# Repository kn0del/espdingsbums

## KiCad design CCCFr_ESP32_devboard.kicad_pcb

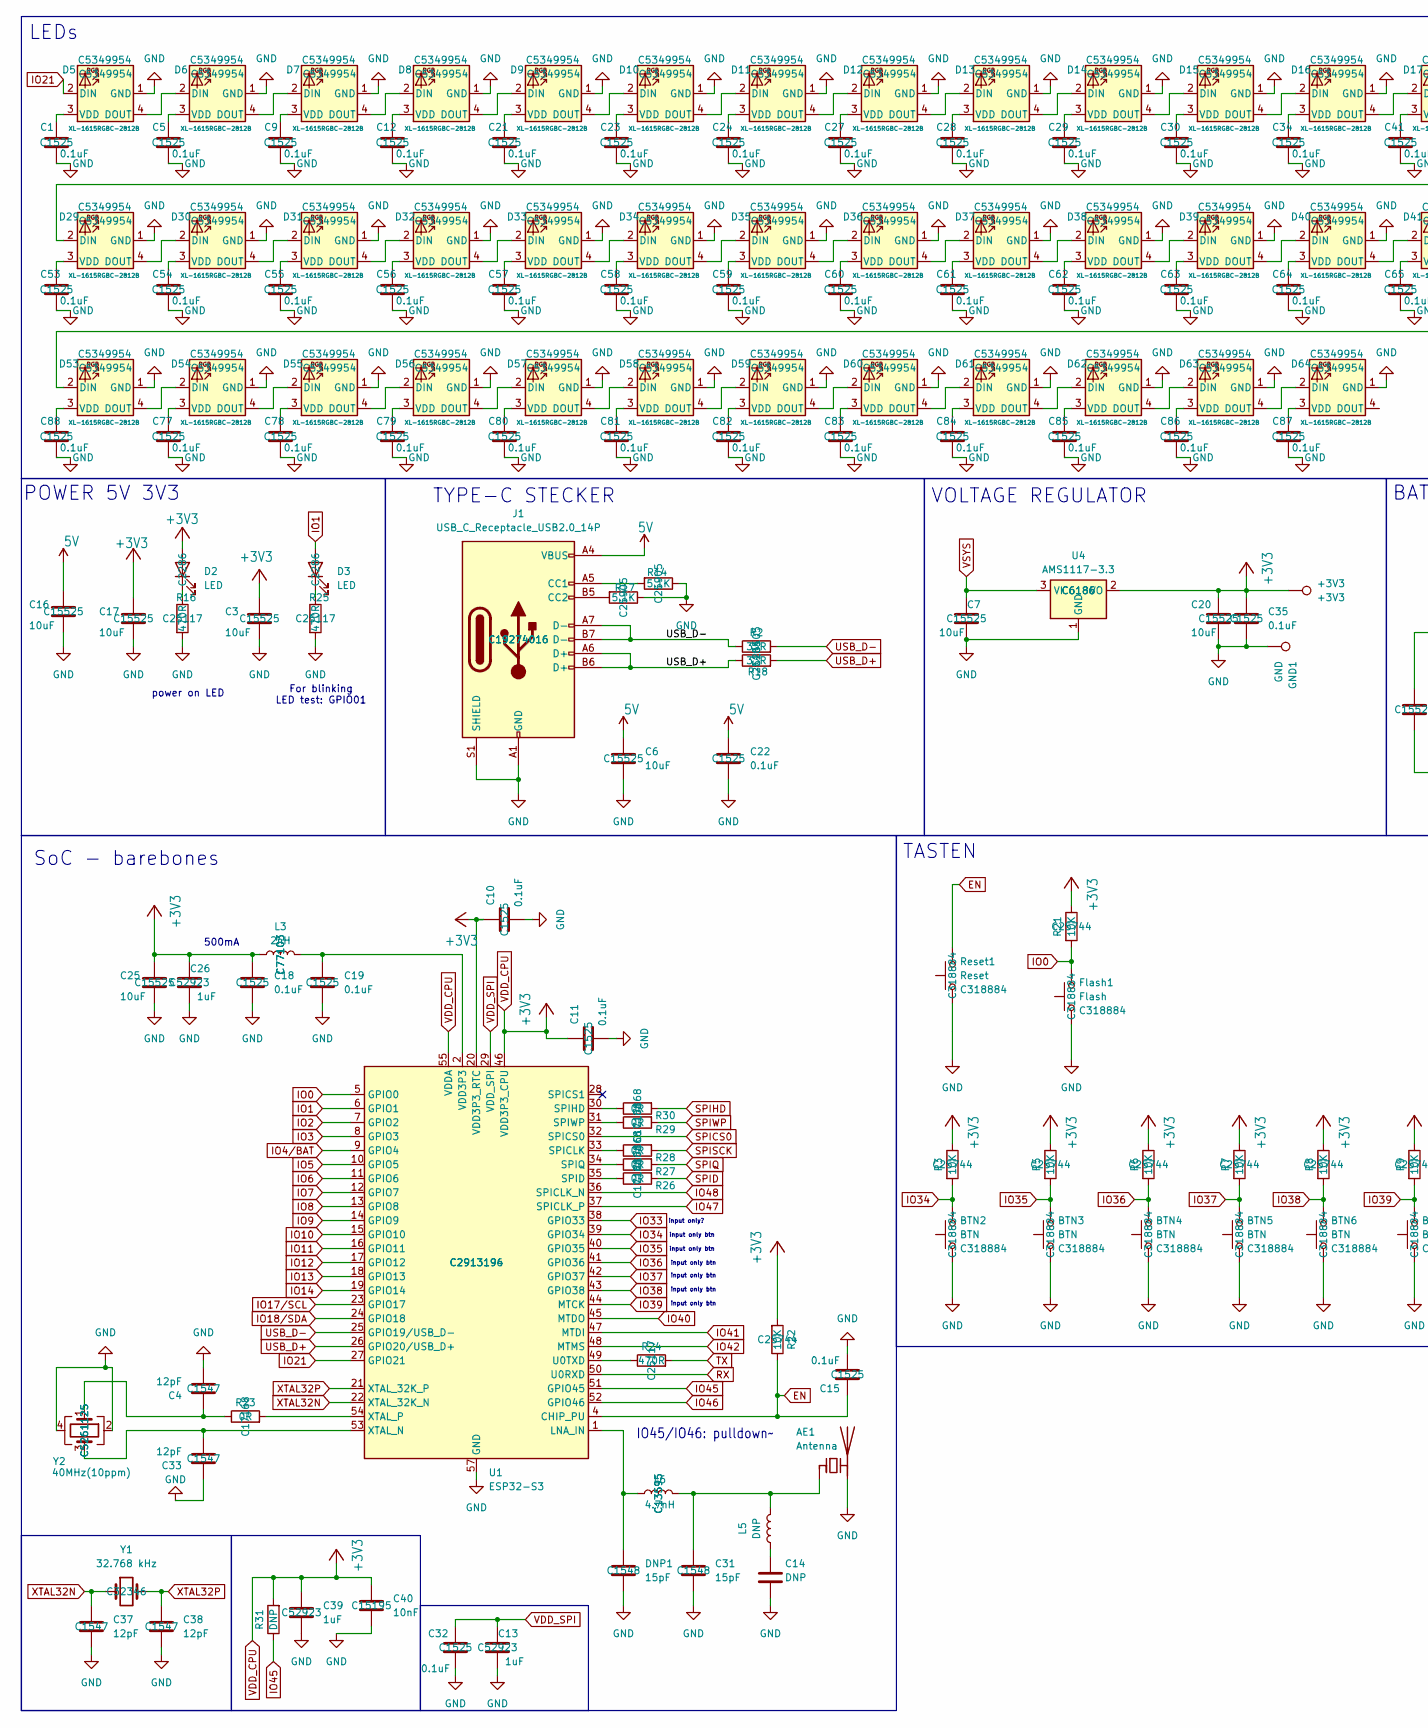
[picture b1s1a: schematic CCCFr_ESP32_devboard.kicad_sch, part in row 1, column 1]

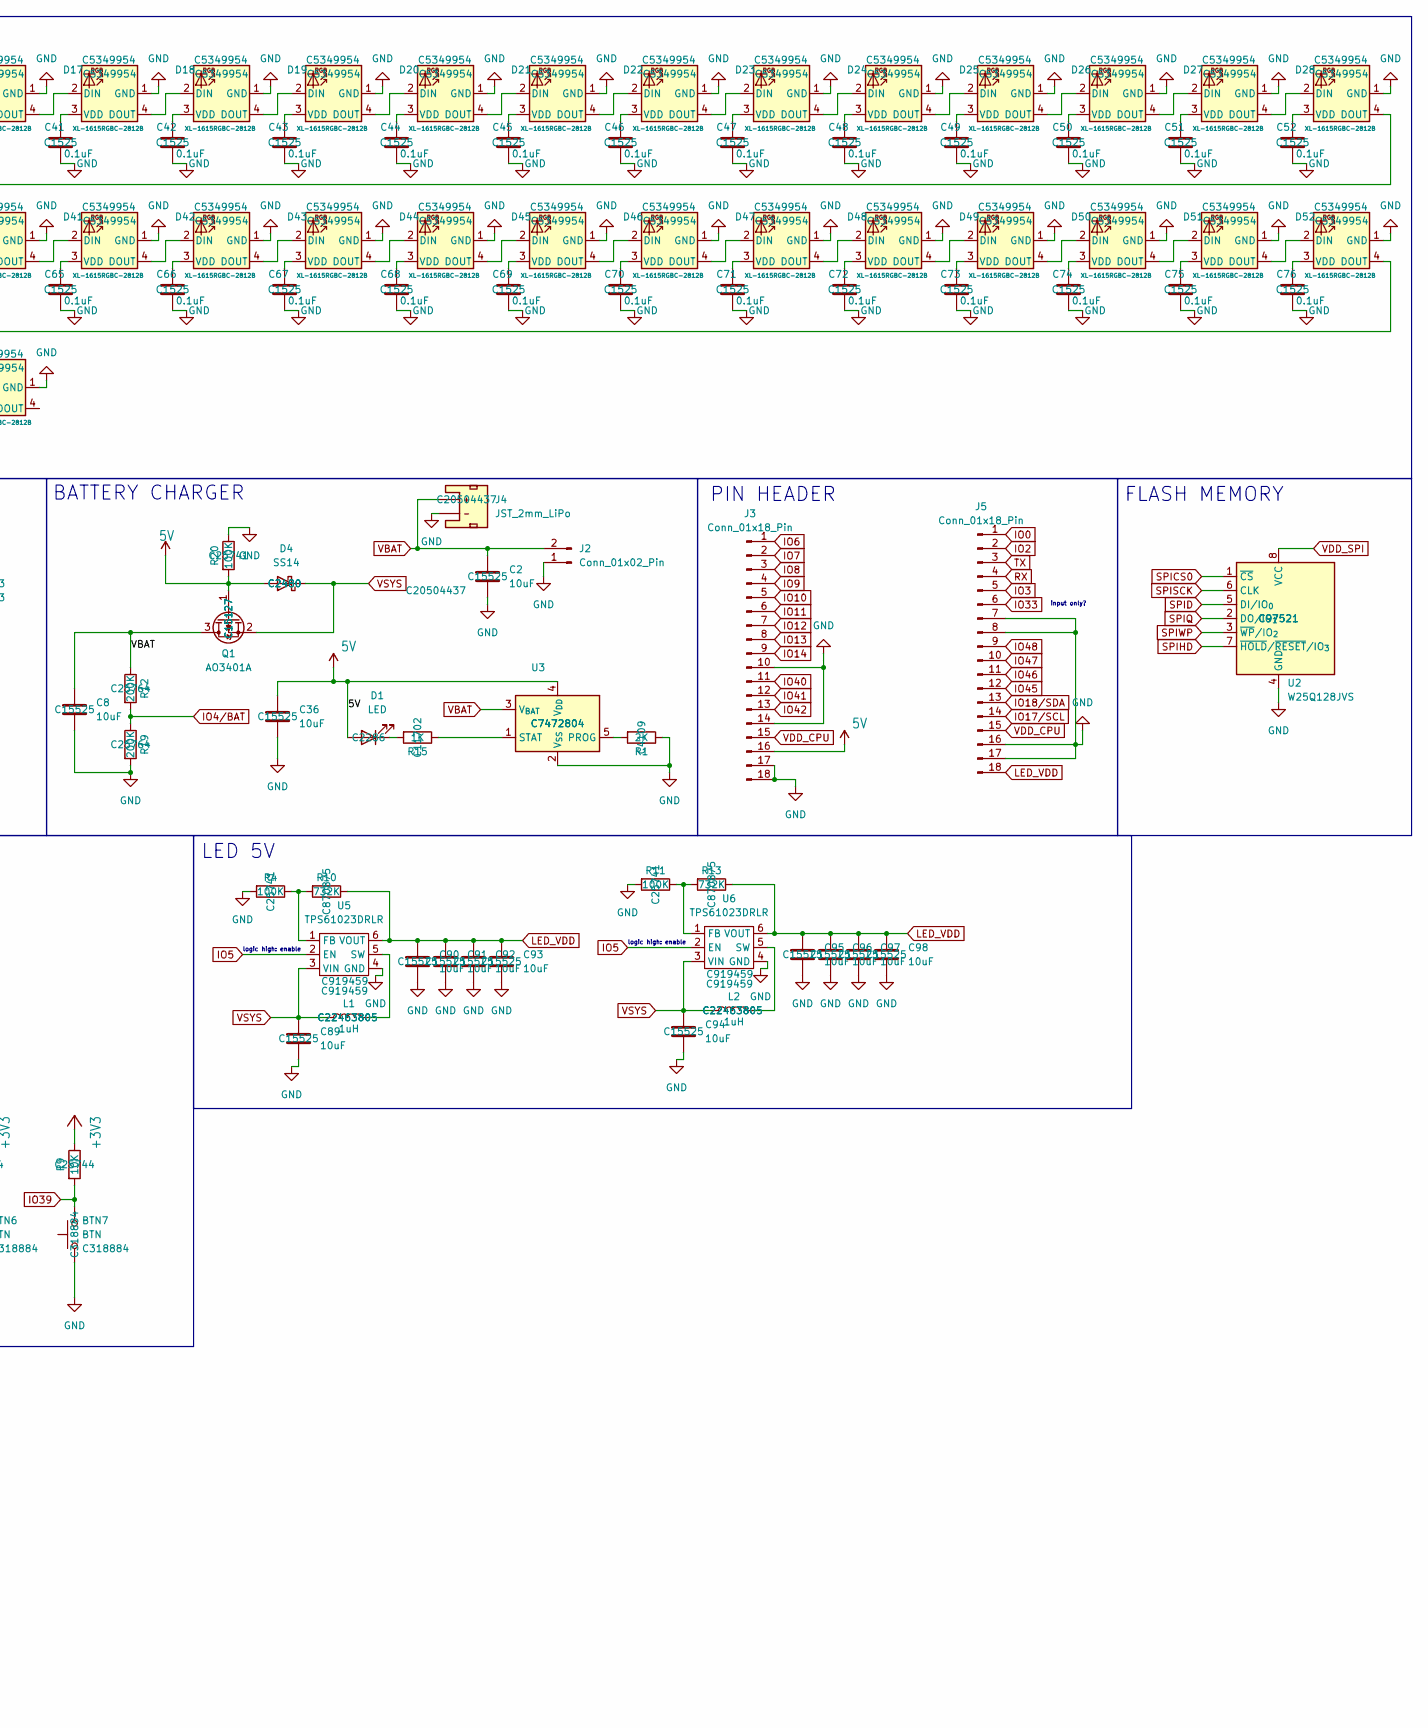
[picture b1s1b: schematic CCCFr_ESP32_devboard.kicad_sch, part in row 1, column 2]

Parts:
+3V3: +3V3; TestPoint_Pad_D1.0mm
AE1: Antenna; Texas_SWRA117D_2.4GHz_Left
BTN2, BTN3, BTN4, BTN5, BTN6, BTN7: BTN; SW_Push_1P1T_XKB_TS-1187A; MNF PART NUMBER C318884; LCSC C318884
C1, C5, C9, C10, C11, C12, C15, C18, C19, C21, C22, C23, C24, C27, C28, C29, C30, C32, C34, C35, C41, C42, C43, C44, C45, C46, C47, C48, C49, C50, C51, C52, C53, C54, C55, C56, C57, C58, C59, C60, C61, C62, C63, C64, C65, C66, C67, C68, C69, C70, C71, C72, C73, C74, C75, C76, C77, C78, C79, C80, C81, C82, C83, C84, C85, C86, C87, C88: 0.1uF; C_0402_1005Metric; MNF PART NUMBER C1525; LCSC C1525
C2, C3, C6, C7, C8, C16, C17, C20, C25, C36, C89, C90, C91, C92, C93, C94, C95, C96, C97, C98: 10uF; C_0402_1005Metric; MNF PART NUMBER C15525; LCSC C15525
C4, C33, C37, C38: 12pF; C_0402_1005Metric; MNF PART NUMBER C1547; LCSC C1547
C13, C26, C39: 1uF; C_0402_1005Metric; MNF PART NUMBER C52923; LCSC C52923
C14: DNP; C_0402_1005Metric
C31: 15pF; C_0402_1005Metric; MNF PART NUMBER C1548; LCSC C1548
C40: 10nF; C_0402_1005Metric; MNF PART NUMBER C15195; LCSC C15195
D1, D2, D3: LED; LED_0603_1608Metric; MNF PART NUMBER C2286; LCSC C2286
D4: SS14; D_SMA; MNF PART NUMBER C2480; LCSC C2480
D5, D6, D7, D8, D9, D10, D11, D12, D13, D14, D15, D16, D17, D18, D19, D20, D21, D22, D23, D24, D25, D26, D27, D28, D29, D30, D31, D32, D33, D34, D35, D36, D37, D38, D39, D40, D41, D42, D43, D44, D45, D46, D47, D48, D49, D50, D51, D52, D53, D54, D55, D56, D57, D58, D59, D60, D61, D62, D63, D64: XL-1615RGBC-2812B; MNF PART NUMBER C5349954; LCSC C5349954
DNP1: 15pF; C_0402_1005Metric; MNF PART NUMBER C1548; LCSC C1548
Flash1: Flash; SW_Push_1P1T_XKB_TS-1187A; MNF PART NUMBER C318884; LCSC C318884
GND1: GND; TestPoint_Pad_D1.0mm
J1: USB_C_Receptacle_USB2.0_14P; USB_C_Receptacle_HCTL_HC-TYPE-C-16P-01A; MNF PART NUMBER C19274016; LCSC C19274016
J2: Conn_01x02_Pin; PinSocket_1x02_P2.54mm_Vertical
J3, J5: Conn_01x18_Pin; PinHeader_1x18_P2.54mm_Vertical
J4: JST_2mm_LiPo; JST_PH_B2B-PH-K_1x02_P2.00mm_Vertical; MNF PART NUMBER C20504437; LCSC C20504437
L1, L2: 1uH; L_TechFuse_SL0420; MNF PART NUMBER C22463805; LCSC C22463805
L3: 2nH; L_0402_1005Metric; MNF PART NUMBER C77103; LCSC C77103
L5: DNP; L_0402_1005Metric
L6: 4.7nH; L_0402_1005Metric; MNF PART NUMBER C13595; LCSC C13595
Q1: AO3401A; SOT-23; MNF PART NUMBER C15127; LCSC C15127
R1: 2K; R_0402_1005Metric; MNF PART NUMBER C4109; LCSC C4109
R2, R18: 33R; R_0402_1005Metric; MNF PART NUMBER C25105; LCSC C25105
R3, R5, R6, R7, R8, R9, R21, R22: 10K; R_0402_1005Metric; MNF PART NUMBER C25744; LCSC C25744
R4, R11, R20: 100K; R_0402_1005Metric; MNF PART NUMBER C25741; LCSC C25741
R10, R13: 732K; R_1206_3216Metric; MNF PART NUMBER C870875; LCSC C870875
R12, R19: 200K; R_0402_1005Metric; MNF PART NUMBER C25764; LCSC C25764
R14, R17: 5.1K; R_0402_1005Metric; MNF PART NUMBER C25905; LCSC C25905
R15: 1K; R_0402_1005Metric; MNF PART NUMBER C11702; LCSC C11702
R16, R24, R25: 470R; R_0402_1005Metric; MNF PART NUMBER C25117; LCSC C25117
R23, R26, R27, R28, R29, R30: 0R; R_0402_1005Metric; MNF PART NUMBER C17168; LCSC C17168
R31: DNP; R_0402_1005Metric
Reset1: Reset; SW_Push_1P1T_XKB_TS-1187A; MNF PART NUMBER C318884; LCSC C318884
U1: ESP32-S3; QFN-56-1EP_7x7mm_P0.4mm_EP4x4mm; MNF PART NUMBER C2913196; LCSC C2913194
U2: W25Q128JVS; SOIC-8_5.3x5.3mm_P1.27mm; MNF PART NUMBER C97521; LCSC C97521
U3: MCP73831-2-OT; SOT-23-5; MNF PART NUMBER C7472804; LCSC C7472804
U4: AMS1117-3.3; SOT-223-3_TabPin2; MNF PART NUMBER C6186; LCSC C6186
U5, U6: TPS61023DRLR; SOT-563; MNF PART NUMBER C919459; LCSC C919459
Y1: 32.768 kHz; Crystal_SMD_3215-2Pin_3.2x1.5mm; MNF PART NUMBER C32346; LCSC C32346
Y2: 40MHz(10ppm); Crystal_SMD_2520-4Pin_2.5x2.0mm; MNF PART NUMBER C5261125; LCSC C5261125

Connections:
5V: C6.1, C16.1, C22.1, C36.1, D1.2 (A), D4.2 (A), J1.A4 (VBUS), J1.A9 (VBUS), J1.B4 (VBUS), J1.B9 (VBUS), J3.16, Q1.1 (G), R20.2, U3.4 (V_{DD})
EN: C15.1, R22.1, Reset1.2, U1.4 (CHIP_PU)
GND: AE1.2 (PCB_Trace), BTN2.1, BTN3.1, BTN4.1, BTN5.1, BTN6.1, BTN7.1, C1.2, C2.2, C3.2, C4.2, C5.2, C6.2, C7.2, C8.2, C9.2, C10.2, C11.2, C12.2, C13.2, C14.2, C15.2, C16.2, C17.2, C18.2, C19.2, C20.2, C21.2, C22.2, C23.2, C24.2, C25.2, C26.2, C27.2, C28.2, C29.2, C30.2, C31.2, C32.2, C33.1, C34.2, C35.2, C36.2, C37.2, C38.2, C39.2, C40.2, C41.2, C42.2, C43.2, C44.2, C45.2, C46.2, C47.2, C48.2, C49.2, C50.2, C51.2, C52.2, C53.2, C54.2, C55.2, C56.2, C57.2, C58.2, C59.2, C60.2, C61.2, C62.2, C63.2, C64.2, C65.2, C66.2, C67.2, C68.2, C69.2, C70.2, C71.2, C72.2, C73.2, C74.2, C75.2, C76.2, C77.2, C78.2, C79.2, C80.2, C81.2, C82.2, C83.2, C84.2, C85.2, C86.2, C87.2, C88.2, C89.2, C90.2, C91.2, C92.2, C93.2, C94.2, C95.2, C96.2, C97.2, C98.2, D5.1 (GND), D6.1 (GND), D7.1 (GND), D8.1 (GND), D9.1 (GND), D10.1 (GND), D11.1 (GND), D12.1 (GND), D13.1 (GND), D14.1 (GND), D15.1 (GND), D16.1 (GND), D17.1 (GND), D18.1 (GND), D19.1 (GND), D20.1 (GND), D21.1 (GND), D22.1 (GND), D23.1 (GND), D24.1 (GND), D25.1 (GND), D26.1 (GND), D27.1 (GND), D28.1 (GND), D29.1 (GND), D30.1 (GND), D31.1 (GND), D32.1 (GND), D33.1 (GND), D34.1 (GND), D35.1 (GND), D36.1 (GND), D37.1 (GND), D38.1 (GND), D39.1 (GND), D40.1 (GND), D41.1 (GND), D42.1 (GND), D43.1 (GND), D44.1 (GND), D45.1 (GND), D46.1 (GND), D47.1 (GND), D48.1 (GND), D49.1 (GND), D50.1 (GND), D51.1 (GND), D52.1 (GND), D53.1 (GND), D54.1 (GND), D55.1 (GND), D56.1 (GND), D57.1 (GND), D58.1 (GND), D59.1 (GND), D60.1 (GND), D61.1 (GND), D62.1 (GND), D63.1 (GND), D64.1 (GND), DNP1.2, Flash1.1, GND1.1, J1.A1 (GND), J1.A12 (GND), J1.B1 (GND), J1.B12 (GND), J1.S1 (SHIELD), J2.1, J3.10, J3.14, J3.17, J3.18, J4.1 (-), J5.7, J5.8, J5.16, J5.17, R1.1, R4.2, R11.2, R14.1, R16.2, R17.1, R19.2, R20.1, R25.2, Reset1.1, U1.57 (GND), U2.4 (GND), U3.2 (V_{SS}), U4.1 (GND), U5.4 (GND), U6.4 (GND), Y2.2, Y2.4
IO0: Flash1.2, J5.1, R21.2, U1.5 (GPIO0)
IO1: D3.2 (A), U1.6 (GPIO1)
IO2: J5.2, U1.7 (GPIO2)
IO3: J5.5, U1.8 (GPIO3)
IO4/BAT: R12.2, R19.1, U1.9 (GPIO4)
IO5: U1.10 (GPIO5), U5.2 (EN), U6.2 (EN)
IO6: J3.1, U1.11 (GPIO6)
IO7: J3.2, U1.12 (GPIO7)
IO8: J3.3, U1.13 (GPIO8)
IO9: J3.4, U1.14 (GPIO9)
IO10: J3.5, U1.15 (GPIO10)
IO11: J3.6, U1.16 (GPIO11)
IO12: J3.7, U1.17 (GPIO12)
IO13: J3.8, U1.18 (GPIO13)
IO14: J3.9, U1.19 (GPIO14)
IO17/SCL: J5.14, U1.23 (GPIO17)
IO18/SDA: J5.13, U1.24 (GPIO18)
IO21: D5.2 (DIN), U1.27 (GPIO21)
IO33: J5.6, U1.38 (GPIO33)
IO34: BTN2.2, R3.2, U1.39 (GPIO34)
IO35: BTN3.2, R5.2, U1.40 (GPIO35)
IO36: BTN4.2, R6.2, U1.41 (GPIO36)
IO37: BTN5.2, R7.2, U1.42 (GPIO37)
IO38: BTN6.2, R8.2, U1.43 (GPIO38)
IO39: BTN7.2, R9.2, U1.44 (MTCK)
IO40: J3.11, U1.45 (MTDO)
IO41: J3.12, U1.47 (MTDI)
IO42: J3.13, U1.48 (MTMS)
IO45: J5.12, R31.1, U1.51 (GPIO45)
IO46: J5.11, U1.52 (GPIO46)
IO47: J5.10, U1.37 (SPICLK_P)
IO48: J5.9, U1.36 (SPICLK_N)
LED_VDD: C90.1, C91.1, C92.1, C93.1, C95.1, C96.1, C97.1, C98.1, J5.18, R10.1, R13.1, U5.6 (VOUT), U6.6 (VOUT)
unnamed: AE1.1 (FEED), C31.1, L5.2, L6.2
unnamed: C4.1, R23.1, Y2.1
unnamed: C14.1, L5.1
unnamed: C19.1, L3.2, U1.2 (VDD3P3), U1.3 (VDD3P3)
unnamed: D1.1 (K), R15.2
unnamed: D2.1 (K), R16.1
unnamed: D3.1 (K), R25.1
unnamed: D5.4 (DOUT), D6.2 (DIN)
unnamed: C1.1, D5.3 (VDD)
unnamed: D6.4 (DOUT), D7.2 (DIN)
unnamed: C5.1, D6.3 (VDD)
unnamed: D7.4 (DOUT), D8.2 (DIN)
unnamed: C9.1, D7.3 (VDD)
unnamed: D8.4 (DOUT), D9.2 (DIN)
unnamed: C12.1, D8.3 (VDD)
unnamed: C21.1, D9.3 (VDD)
unnamed: D9.4 (DOUT), D10.2 (DIN)
unnamed: D10.4 (DOUT), D11.2 (DIN)
unnamed: C23.1, D10.3 (VDD)
unnamed: D11.4 (DOUT), D12.2 (DIN)
unnamed: C24.1, D11.3 (VDD)
unnamed: D12.4 (DOUT), D13.2 (DIN)
unnamed: C27.1, D12.3 (VDD)
unnamed: D13.4 (DOUT), D14.2 (DIN)
unnamed: C28.1, D13.3 (VDD)
unnamed: D14.4 (DOUT), D15.2 (DIN)
unnamed: C29.1, D14.3 (VDD)
unnamed: D15.4 (DOUT), D16.2 (DIN)
unnamed: C30.1, D15.3 (VDD)
unnamed: D16.4 (DOUT), D17.2 (DIN)
unnamed: C34.1, D16.3 (VDD)
unnamed: D17.4 (DOUT), D18.2 (DIN)
unnamed: C41.1, D17.3 (VDD)
unnamed: D18.4 (DOUT), D19.2 (DIN)
unnamed: C42.1, D18.3 (VDD)
unnamed: D19.4 (DOUT), D20.2 (DIN)
unnamed: C43.1, D19.3 (VDD)
unnamed: D20.4 (DOUT), D21.2 (DIN)
unnamed: C44.1, D20.3 (VDD)
unnamed: D21.4 (DOUT), D22.2 (DIN)
unnamed: C45.1, D21.3 (VDD)
unnamed: D22.4 (DOUT), D23.2 (DIN)
unnamed: C46.1, D22.3 (VDD)
unnamed: D23.4 (DOUT), D24.2 (DIN)
unnamed: C47.1, D23.3 (VDD)
unnamed: D24.4 (DOUT), D25.2 (DIN)
unnamed: C48.1, D24.3 (VDD)
unnamed: D25.4 (DOUT), D26.2 (DIN)
unnamed: C49.1, D25.3 (VDD)
unnamed: D26.4 (DOUT), D27.2 (DIN)
unnamed: C50.1, D26.3 (VDD)
unnamed: D27.4 (DOUT), D28.2 (DIN)
unnamed: C51.1, D27.3 (VDD)
unnamed: D28.4 (DOUT), D29.2 (DIN)
unnamed: C52.1, D28.3 (VDD)
unnamed: D29.4 (DOUT), D30.2 (DIN)
unnamed: C53.1, D29.3 (VDD)
unnamed: D30.4 (DOUT), D31.2 (DIN)
unnamed: C54.1, D30.3 (VDD)
unnamed: D31.4 (DOUT), D32.2 (DIN)
unnamed: C55.1, D31.3 (VDD)
unnamed: D32.4 (DOUT), D33.2 (DIN)
unnamed: C56.1, D32.3 (VDD)
unnamed: D33.4 (DOUT), D34.2 (DIN)
unnamed: C57.1, D33.3 (VDD)
unnamed: D34.4 (DOUT), D35.2 (DIN)
unnamed: C58.1, D34.3 (VDD)
unnamed: D35.4 (DOUT), D36.2 (DIN)
unnamed: C59.1, D35.3 (VDD)
unnamed: D36.4 (DOUT), D37.2 (DIN)
unnamed: C60.1, D36.3 (VDD)
unnamed: D37.4 (DOUT), D38.2 (DIN)
unnamed: C61.1, D37.3 (VDD)
unnamed: D38.4 (DOUT), D39.2 (DIN)
unnamed: C62.1, D38.3 (VDD)
unnamed: D39.4 (DOUT), D40.2 (DIN)
unnamed: C63.1, D39.3 (VDD)
unnamed: D40.4 (DOUT), D41.2 (DIN)
unnamed: C64.1, D40.3 (VDD)
unnamed: D41.4 (DOUT), D42.2 (DIN)
unnamed: C65.1, D41.3 (VDD)
unnamed: D42.4 (DOUT), D43.2 (DIN)
unnamed: C66.1, D42.3 (VDD)
unnamed: D43.4 (DOUT), D44.2 (DIN)
unnamed: C67.1, D43.3 (VDD)
unnamed: D44.4 (DOUT), D45.2 (DIN)
unnamed: C68.1, D44.3 (VDD)
unnamed: D45.4 (DOUT), D46.2 (DIN)
unnamed: C69.1, D45.3 (VDD)
unnamed: D46.4 (DOUT), D47.2 (DIN)
unnamed: C70.1, D46.3 (VDD)
unnamed: D47.4 (DOUT), D48.2 (DIN)
unnamed: C71.1, D47.3 (VDD)
unnamed: D48.4 (DOUT), D49.2 (DIN)
unnamed: C72.1, D48.3 (VDD)
unnamed: D49.4 (DOUT), D50.2 (DIN)
unnamed: C73.1, D49.3 (VDD)
unnamed: D50.4 (DOUT), D51.2 (DIN)
unnamed: C74.1, D50.3 (VDD)
unnamed: D51.4 (DOUT), D52.2 (DIN)
unnamed: C75.1, D51.3 (VDD)
unnamed: D52.4 (DOUT), D53.2 (DIN)
unnamed: C76.1, D52.3 (VDD)
unnamed: D53.4 (DOUT), D54.2 (DIN)
unnamed: C88.1, D53.3 (VDD)
unnamed: D54.4 (DOUT), D55.2 (DIN)
unnamed: C77.1, D54.3 (VDD)
unnamed: D55.4 (DOUT), D56.2 (DIN)
unnamed: C78.1, D55.3 (VDD)
unnamed: D56.4 (DOUT), D57.2 (DIN)
unnamed: C79.1, D56.3 (VDD)
unnamed: D57.4 (DOUT), D58.2 (DIN)
unnamed: C80.1, D57.3 (VDD)
unnamed: D58.4 (DOUT), D59.2 (DIN)
unnamed: C81.1, D58.3 (VDD)
unnamed: D59.4 (DOUT), D60.2 (DIN)
unnamed: C82.1, D59.3 (VDD)
unnamed: D60.4 (DOUT), D61.2 (DIN)
unnamed: C83.1, D60.3 (VDD)
unnamed: D61.4 (DOUT), D62.2 (DIN)
unnamed: C84.1, D61.3 (VDD)
unnamed: D62.4 (DOUT), D63.2 (DIN)
unnamed: C85.1, D62.3 (VDD)
unnamed: D63.4 (DOUT), D64.2 (DIN)
unnamed: C86.1, D63.3 (VDD)
unnamed: C87.1, D64.3 (VDD)
unnamed: J1.A5 (CC1), R14.2
unnamed: J1.B5 (CC2), R17.2
unnamed: DNP1.1, L6.1, U1.1 (LNA_IN)
unnamed: R28.1, U1.33 (SPICLK)
unnamed: R26.1, U1.35 (SPID)
unnamed: R30.1, U1.30 (SPIHD)
unnamed: R27.1, U1.34 (SPIQ)
unnamed: R29.1, U1.31 (SPIWP)
unnamed: R24.1, U1.49 (U0TXD)
unnamed: C33.2, U1.53 (XTAL_N), Y2.3
unnamed: R23.2, U1.54 (XTAL_P)
unnamed: R1.2, U3.5 (PROG)
unnamed: R15.1, U3.1 (STAT)
unnamed: R4.1, R10.2, U5.1 (FB)
unnamed: L1.2, U5.5 (SW)
unnamed: R11.1, R13.2, U6.1 (FB)
unnamed: L2.2, U6.5 (SW)
RX: J5.4, U1.50 (U0RXD)
SPICS0: U1.32 (SPICS0), U2.1 (~CS)
SPID: R26.2, U2.5 (DI/IO_{0})
SPIHD: R30.2, U2.7 (~HOLD/~RESET/IO_{3})
SPIQ: R27.2, U2.2 (DO/IO_{1})
SPISCK: R28.2, U2.6 (CLK)
SPIWP: R29.2, U2.3 (~WP/IO_{2})
TX: J5.3, R24.2
USB_D+: J1.A6 (D+), J1.B6 (D+), R18.1, R18.2, U1.26 (GPIO20/USB_D+)
USB_D-: J1.A7 (D-), J1.B7 (D-), R2.1, R2.2, U1.25 (GPIO19/USB_D-)
VBAT: C2.1, C8.1, J2.2, J4.2 (+), Q1.3 (D), R12.1, U3.3 (V_{BAT})
VDD_CPU: +3V3.1, C3.1, C10.1, C11.1, C17.1, C18.1, C20.1, C25.1, C26.1, C35.1, C39.1, C40.1, D2.2 (A), J3.15, J5.15, L3.1, R3.1, R5.1, R6.1, R7.1, R8.1, R9.1, R21.1, R22.2, R31.2, U1.20 (VDD3P3_RTC), U1.46 (VDD3P3_CPU), U1.55 (VDDA), U1.56 (VDDA), U4.2 (VO)
VDD_SPI: C13.1, C32.1, U1.29 (VDD_SPI), U2.8 (VCC)
VSYS: C7.1, C89.1, C94.1, D4.1 (K), L1.1, L2.1, Q1.2 (S), U4.3 (VI), U5.3 (VIN), U6.3 (VIN)
XTAL32N: C37.1, U1.22 (XTAL_32K_N), Y1.1
XTAL32P: C38.1, U1.21 (XTAL_32K_P), Y1.2

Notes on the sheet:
BATTERY CHARGER
VOLTAGE REGULATOR
input only btn
power on LED
500mA
LEDs
SoC - barebones
PIN HEADER
FLASH MEMORY
logic high: enable
input only?
LED 5V
TASTEN
For blinking LED test: GPIO01
POWER 5V 3V3
IO45/IO46: pulldown~~{}
TYPE-C STECKER

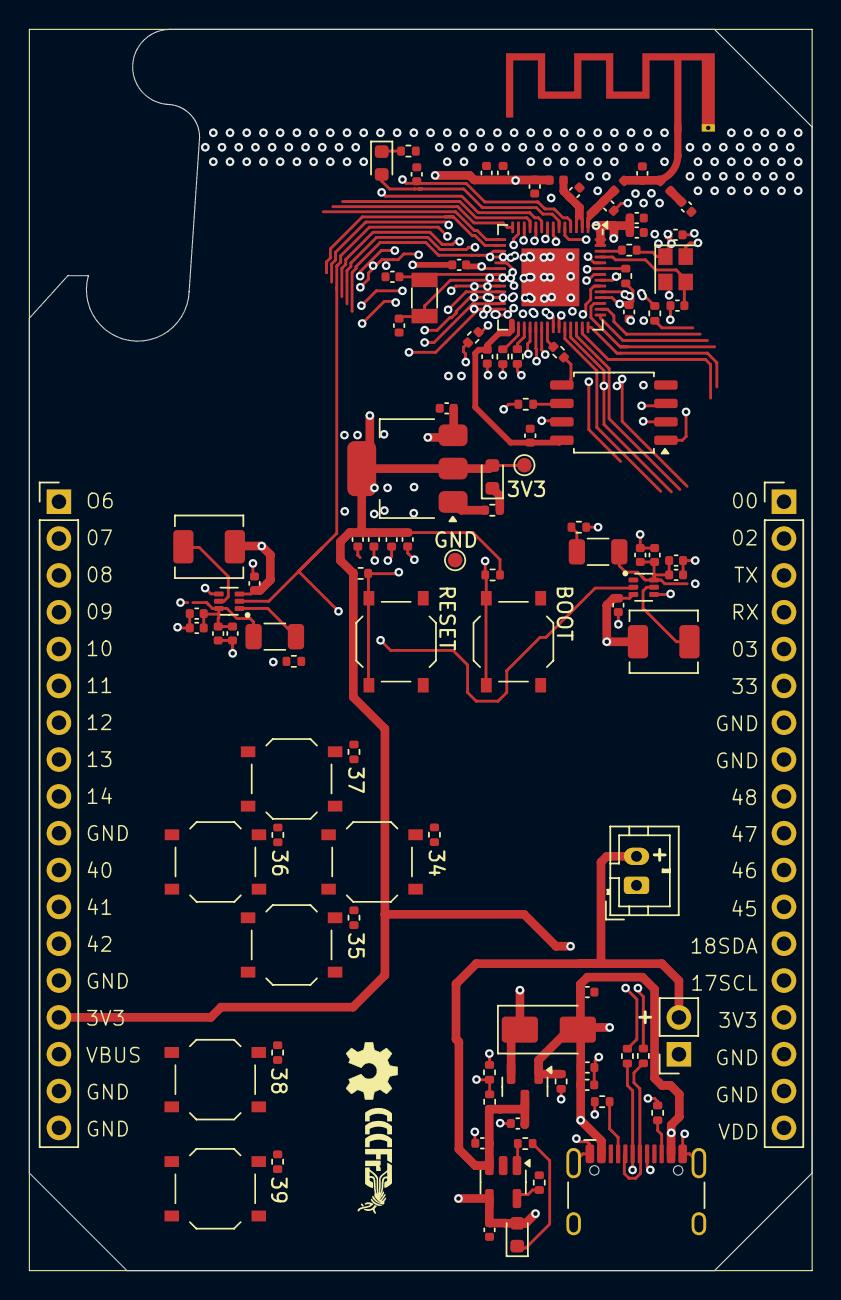
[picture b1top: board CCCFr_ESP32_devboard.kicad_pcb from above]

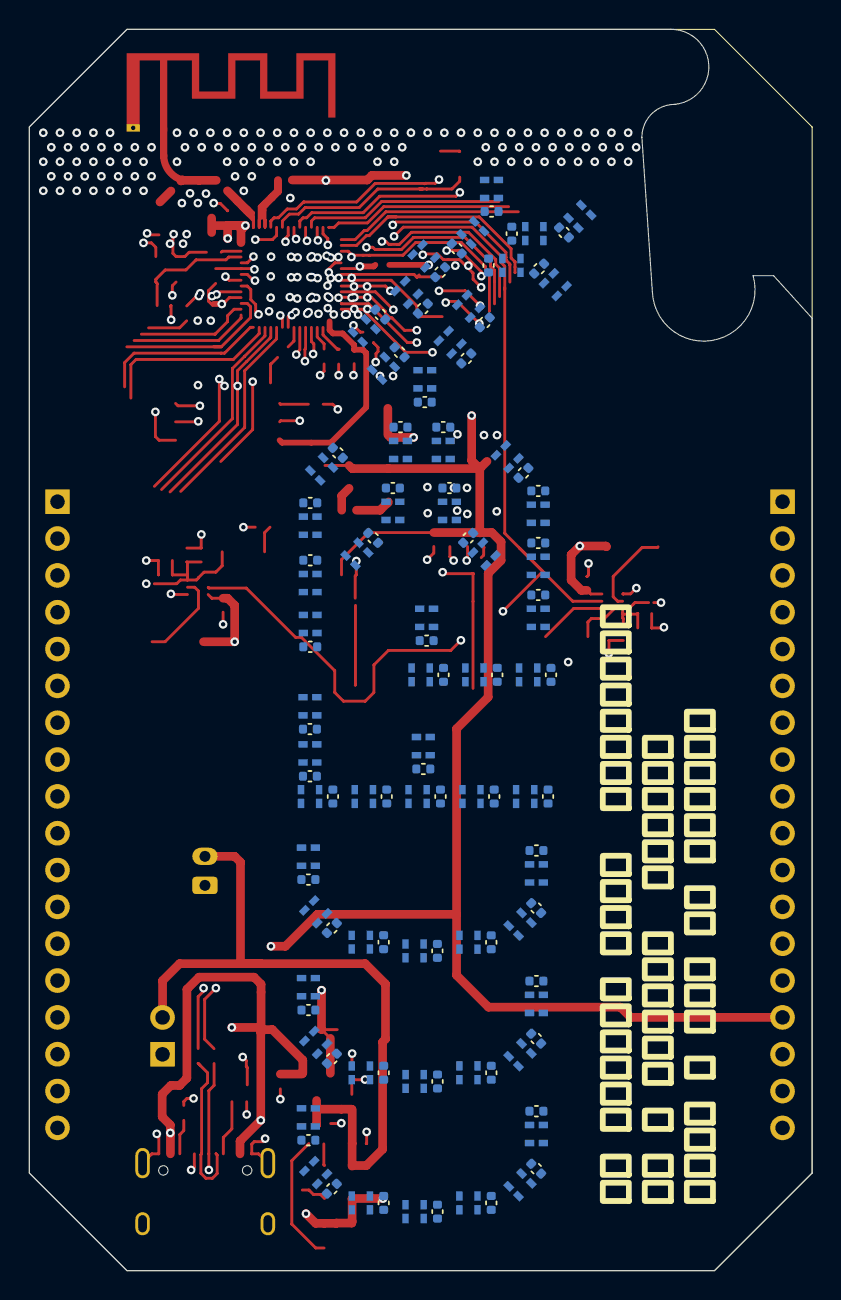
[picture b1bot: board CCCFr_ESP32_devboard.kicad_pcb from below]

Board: 4 copper layers, 54.0 x 85.6 mm, 225 parts (120 on the bottom side), 195 nets.

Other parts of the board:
Ref**: Val**; OSHW_Logo_4mm

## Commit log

2025-12-02 added guideline
2025-12-02 added info to readme
2025-12-02 added extra memory
2025-12-04 integrated bottle opener
2025-12-05 switchewd to kicad 9
2025-12-05 added antenna model WIP
2025-12-17 added bottle opener
2025-12-26 Added 60 pieces of 2812B in the shape of CCCFr
2025-12-26 Added buttons
2025-12-28 rearrandged footprints
2025-12-28 Added JST plug for battery
2025-12-28 routed a bit
2025-12-29 added some instructions
2026-01-03 did some routing
